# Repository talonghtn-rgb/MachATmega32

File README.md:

# ATmega32 Embedded Learning Board

<h2 align="center">
  THIẾT KẾ VÀ CHẾ TẠO BO MẠCH LẬP TRÌNH NHÚNG DỰA TRÊN VI ĐIỀU KHIỂN AVR CHO MỤC ĐÍCH GIÁO DỤC
</h2>

<p align="center">
  <b>ATmega32 Embedded Training Board</b>
</p>

---

##  Giới thiệu

Đây là dự án thiết kế và chế tạo **bo mạch học tập lập trình nhúng sử dụng vi điều khiển ATmega32**, được xây dựng nhằm phục vụ việc học tập, thực hành và nghiên cứu các hệ thống nhúng.

Bo mạch tích hợp nhiều ngoại vi phổ biến, giúp sinh viên có thể thực hành lập trình vi điều khiển, giao tiếp với cảm biến, thiết bị hiển thị, bộ nhớ và các chuẩn giao tiếp thông dụng.

Toàn bộ sơ đồ nguyên lý và PCB của bo mạch được thiết kế bằng **KiCad**.

---

##  Mục tiêu

- Thiết kế một bo mạch học tập dựa trên vi điều khiển **ATmega32**.
- Tích hợp các ngoại vi thường sử dụng trong các bài thực hành vi điều khiển.
- Hỗ trợ nhiều chuẩn giao tiếp như UART, I2C, SPI và 1-Wire.
- Thiết kế PCB hoàn chỉnh bằng KiCad.
- Xây dựng nền tảng phần cứng phục vụ các bài thực hành lập trình nhúng.
- Kiểm thử từng chức năng của bo mạch trên phần cứng thực tế.

---

##  Vi điều khiển:  ATmega32

##  Các ngoại vi tích hợp

Bo mạch được thiết kế với các khối chức năng:

| Ngoại vi | Chức năng |
|---|---|
| LCD 16x2 | Hiển thị thông tin |
| LED 7 đoạn 4 số | Hiển thị số |
| LM35 | Đo nhiệt độ |
| DS18B20 | Cảm biến nhiệt độ |
| DS3231 | Đồng hồ thời gian thực |
| Relay | Điều khiển thiết bị |
| Micro SD Card | Lưu trữ dữ liệu |
| LED đơn | Hiển thị trạng thái |
| Button | Nhập tín hiệu số |
| Potentiometer | Tạo tín hiệu analog |
| LDR | Đo cường độ ánh sáng |
| CH340E | Giao tiếp USB-UART |

Các ngoại vi trên được tích hợp nhằm phục vụ nhiều bài thực hành về GPIO, ADC, UART, I2C, SPI, 1-Wire và điều khiển thiết bị.

---

##  Các chuẩn giao tiếp
UART,I2C,SPI,1-Wire

##  Thiết kế bằng KiCad

Project được thiết kế bằng **KiCad 9**.

Các file chính:

```text
ATmega32/
│
├── atmega32.kicad_pro       # KiCad Project
├── atmega32.kicad_sch       # Schematic
├── atmega32.kicad_pcb       # PCB Layout
│
├── aa.kicad_sym             # Custom Symbol Library
│
├── CR1220 SMD.pretty/       # Footprint Library
├── Micro.pretty/            # Footprint Library
├── SN74LVC125APWR.pretty/   # Footprint Library
│
├── fp-lib-table
├── sym-lib-table
└── Logo_hus.png
```

## Hình ảnh sản phẩm trong quá trình làm
## Ghi chú: Hình ảnh ở trên là bản đầu tiên làm, file ở trên đã sửa sau khi test các chức năng sửa những lỗi cho ra bản hoàn chỉnh nhất.

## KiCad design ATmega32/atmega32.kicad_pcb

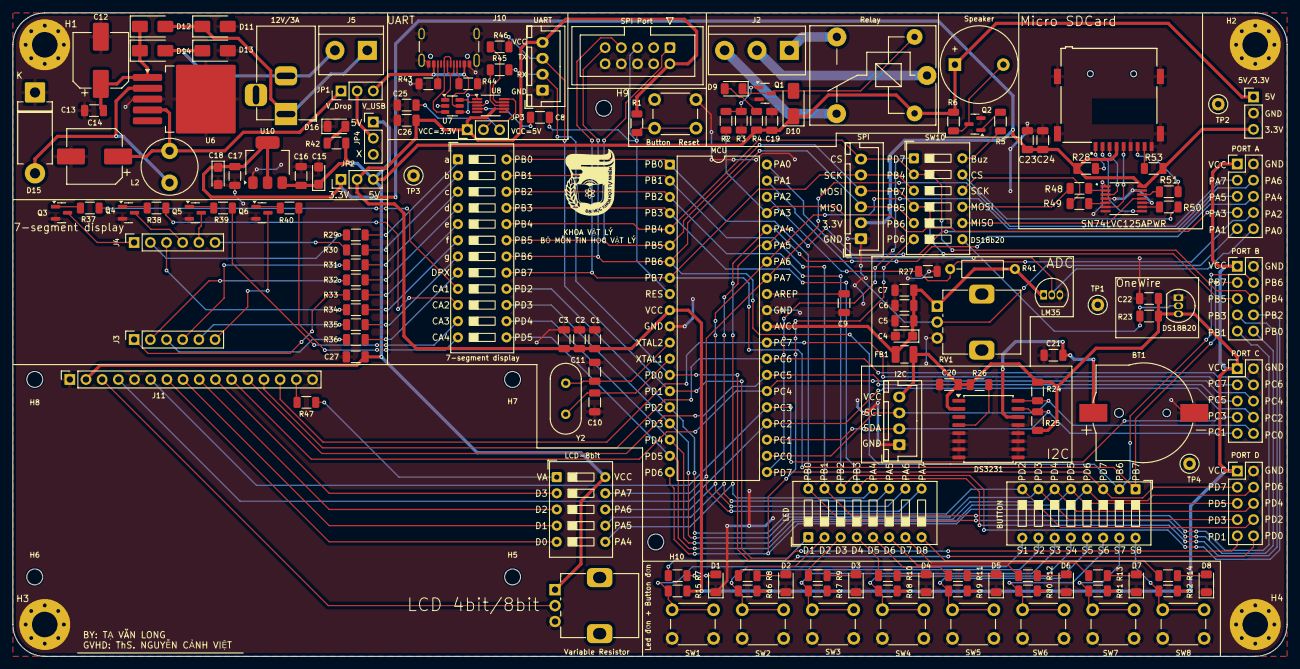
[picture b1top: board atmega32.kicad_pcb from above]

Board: 2 copper layers, 200.0 x 101.0 mm, 168 parts (0 on the bottom side), 145 nets.

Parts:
5V/3.3V: 5V/3.3V; PinHeader_1x03_P2.54mm_Vertical
7-segment display: LED7_DOAN_4SO; SW_DIP_SPSTx12_Slide_9.78x32.66mm_W7.62mm_P2.54mm
12V/3A: Barrel_Jack; BarrelJack_Horizontal
 : LOGO
BT1: PIN; BatteryHolder_RSPRO_2378296_1x1220
BUTTON: BUTTON_DON; SW_DIP_SPSTx08_Slide_9.78x22.5mm_W7.62mm_P2.54mm
Button  Reset: SW_Push; SW_PUSH_6mm_H5mm
C1, C2, C3, C5, C6, C7, C8, C9, C16, C17, C19, C20, C21, C22, C24, C26, C27: 100nF; C_1206_3216Metric
C4, C15, C18: 10uF; CP_EIA-3216-18_Kemet-A
C10, C11: 22pF; C_1206_3216Metric
C12: 440uF/35V; CP_Elec_8x10.5
C13: 1000nF; C_1206_3216Metric
C14: 330uF/35V; CP_Elec_8x10.5
C23: 10uF; C_1206_3216Metric
C25: 10nF; C_1206_3216Metric
D1, D2, D3, D4, D5, D6, D7, D8, D9, D16: LED; LED_1206_3216Metric
D10, D11, D12, D13, D14: 1N4007; D_SMA
D15: 1N5822; D_DO-201AD_P12.70mm_Horizontal
DS18B20: DS18B20; TO-92_Inline
DS3231: DS3231M; SOIC-16W_7.5x10.3mm_P1.27mm
FB1: FerriteBead; L_1210_3225Metric
H1: MH1; MountingHole_4mm_Pad_Via
H2: MH2; MountingHole_4mm_Pad_Via
H3: MH3; MountingHole_4mm_Pad_Via
H4: MH4; MountingHole_4mm_Pad_Via
H5: LCD1; MountingHole_2.5mm
H6: LCD2; MountingHole_2.5mm
H7: LCD3; MountingHole_2.5mm
H8: LCD4; MountingHole_2.5mm
H9: MH5; MountingHole_2.5mm
H10: MH6; MountingHole_2.5mm
I2C: SCL/SDA; JST_XH_B4B-XH-A_1x04_P2.50mm_Vertical
J1: Micro_SD_Card; GCT_MEM2075
J2: Screw_Terminal_01x03; TerminalBlock_bornier-3_P5.08mm
J3: 4-digit 7-segment_2; PinSocket_1x06_P2.54mm_Vertical
J4: 4-digit 7-segment_1; PinSocket_1x06_P2.54mm_Vertical
J5: Screw_Terminal_01x02; TerminalBlock_bornier-2_P5.08mm
J10: USB_C_Receptacle_USB2.0_16P; USB_C_Receptacle_GCT_USB4105-xx-A_16P_TopMnt_Horizontal
J11: Conn_01x16_lcd; PinSocket_1x16_P2.54mm_Vertical
JP1: Nguồn lọc or USB; PinHeader_1x03_P2.54mm_Vertical
JP2, JP3: 5V or 3.3V; PinHeader_1x03_P2.54mm_Vertical
JP4: 5V or x; PinHeader_1x03_P2.54mm_Vertical
L2: 33uH; L_Radial_D8.7mm_P5.00mm_Fastron_07HCP
LCD-8bit: SW_LCD_8bit; SW_DIP_SPSTx05_Slide_9.78x14.88mm_W7.62mm_P2.54mm
LED: LED_DON; SW_DIP_SPSTx08_Slide_9.78x22.5mm_W7.62mm_P2.54mm
LM35: LM35-LP; TO-92_Inline
MCU: ATmega32A-P; DIP-40_W15.24mm
PORT A: Port A; PinHeader_2x05_P2.54mm_Vertical
PORT B: Port B; PinHeader_2x05_P2.54mm_Vertical
PORT C: Port C; PinHeader_2x05_P2.54mm_Vertical
PORT D: Port D; PinHeader_2x05_P2.54mm_Vertical
Q1: MMBT2222A; SOT-23
Q2, Q3, Q4, Q5, Q6: BC846; SOT-23
R1, R15, R16, R17, R18, R19, R20, R21, R22, R26, R27, R37, R38, R39, R40: 10K; R_1206_3216Metric
R2, R5, R6, R45, R46: 1K; R_1206_3216Metric
R3: 10k; R_1206_3216Metric
R4: 470; R_1206_3216Metric
R7, R8, R9, R10, R11, R12, R13, R14: 330; R_1206_3216Metric
R23: 4.7k; R_1206_3216Metric
R24, R25, R28, R53: 4.7K; R_1206_3216Metric
R29, R30, R31, R32, R33, R34, R35, R36, R47: 220; R_1206_3216Metric
R41: GL5528 photoresistor; R_Axial_DIN0207_L6.3mm_D2.5mm_P10.16mm_Horizontal
R42: 2.2K; R_1206_3216Metric
R43, R44: 5k1; R_1206_3216Metric
R48, R49, R50, R51: 3.3K; R_1206_3216Metric
RV1: R_Potentiometer; Potentiometer_Alps_RK09K_Single_Vertical
Relay: SANYOU_SRD; Relay_SPDT_SANYOU_SRD_Series_Form_C
SN74LVC125APWR: SN74LVC125APWR; SOP65P640X120-14N
SPI: SPI; JST_XH_B6B-XH-A_1x06_P2.50mm_Vertical
SPI Port: AVR-ISP-10; IDC-Header_2x05_P2.54mm_Vertical
SW1, SW2, SW3, SW4, SW5, SW6, SW7, SW8: SW_Push; SW_PUSH_6mm_H5mm
SW10: SW_DIP_x06; SW_DIP_SPSTx06_Slide_9.78x17.42mm_W7.62mm_P2.54mm
Speaker: Buzzer; Buzzer_12x9.5RM7.6
TP1, TP2, TP3, TP4: TestPoint; TestPoint_Loop_D2.50mm_Drill1.0mm
U6: LM2596S-ADJ; TO-263-5_TabPin3
U7: USBLC6-2SC6; SOT-23-6
U8: CH340E; MSOP-10_3x3mm_P0.5mm
U10: LM1117MP-3.3; SOT-223-3_TabPin2
UART: TX/RX; JST_XH_B4B-XH-A_1x04_P2.50mm_Vertical
Variable Resistor: 10K; Potentiometer_Alps_RK09K_Single_Vertical
Y2: 8Mhz; Crystal_HC49-U_Vertical

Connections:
/Buz: R5.1, SW10.12
/CA1: J4.1, Q3.3 (C)
/CA2: J4.4, Q4.3 (C)
/CA3: J4.5, Q5.3 (C)
/CA4: J3.6, Q6.3 (C)
/CD: J1.2 (DAT3/CD), SN74LVC125APWR.8 (3Y)
/CLK: J1.5 (CLK), SN74LVC125APWR.6 (2Y)
/CMD: J1.3 (CMD), SN74LVC125APWR.3 (1Y)
/CS: R50.2, SW10.11
/D0: J1.7 (DAT0), R51.2
/D1: LED.1, R7.2
/D2: LED.2, R8.2
/D3: LED.3, R9.2
/D4: LED.4, R10.2
/D5: LED.5, R11.2
/D6: LED.6, R12.2
/D7: LED.7, R13.2
/D8: LED.8, R14.2
/DPX: J3.3, R36.2
/DS18b20: DS18B20.2 (DQ), R23.1, SW10.7
/LCD_D0: J11.7, LCD-8bit.5
/LCD_D1: J11.8, LCD-8bit.4
/LCD_D2: J11.9, LCD-8bit.3
/LCD_D3: J11.10, LCD-8bit.2
/LED7_D1: 7-segment display.9, R37.1
/LED7_D2: 7-segment display.10, R38.1
/LED7_D3: 7-segment display.11, R39.1
/LED7_D4: 7-segment display.12, R40.1
/LED7_DPX: 7-segment display.8, R36.1
/LED7_a: 7-segment display.1, R29.1
/LED7_b: 7-segment display.2, R30.1
/LED7_c: 7-segment display.3, R31.1
/LED7_d: 7-segment display.4, R32.1
/LED7_e: 7-segment display.5, R33.1
/LED7_f: 7-segment display.6, R34.1
/LED7_g: 7-segment display.7, R35.1
/MISO: SN74LVC125APWR.11 (4Y), SW10.8
/MOSI: R48.2, SW10.9
/PA0: LM35.2 (V_{OUT}), MCU.40 (PA0), PORT A.10
/PA1: MCU.39 (PA1), PORT A.9, RV1.2
/PA2: MCU.38 (PA2), PORT A.8, R27.1, R41.2
/PA3: MCU.37 (PA3), PORT A.7, R2.1
/PA4: LCD-8bit.6, LED.12, MCU.36 (PA4), PORT A.6
/PA5: LCD-8bit.7, LED.11, MCU.35 (PA5), PORT A.5
/PA6: LCD-8bit.8, LED.10, MCU.34 (PA6), PORT A.4
/PA7: LCD-8bit.9, LED.9, MCU.33 (PA7), PORT A.3
/PB0: 7-segment display.24, LED.16, MCU.1 (PB0), PORT B.10
/PB1: 7-segment display.23, LED.15, MCU.2 (PB1), PORT B.9
/PB2: 7-segment display.22, LED.14, MCU.3 (PB2), PORT B.8
/PB3: 7-segment display.21, LED.13, MCU.4 (PB3), PORT B.7
/PB4: 7-segment display.20, MCU.5 (PB4), PORT B.6, SPI.6, SW10.2
/PB5: 7-segment display.19, MCU.6 (PB5), PORT B.5, SPI.4, SPI Port.1 (MOSI), SW10.4
/PB6: 7-segment display.18, BUTTON.2, MCU.7 (PB6), PORT B.4, SPI.3, SPI Port.9 (MISO), SW10.5
/PB7: 7-segment display.17, BUTTON.1, MCU.8 (PB7), PORT B.3, SPI.5, SPI Port.7 (SCK), SW10.3
/PC0: DS3231.16 (SCL), I2C.3, MCU.22 (PC0), PORT C.10, R24.1
/PC1: DS3231.15 (SDA), I2C.2, MCU.23 (PC1), PORT C.9, R25.1
/PC2: J11.4, MCU.24 (PC2), PORT C.8
/PC3: J11.6, MCU.25 (PC3), PORT C.7
/PC4: J11.11, MCU.26 (PC4), PORT C.6
/PC5: J11.12, MCU.27 (PC5), PORT C.5
/PC6: J11.13, MCU.28 (PC6), PORT C.4
/PC7: J11.14, MCU.29 (PC7), PORT C.3
/PD0: MCU.14 (PD0), PORT D.10, R45.2, UART.2
/PD1: MCU.15 (PD1), PORT D.9, R46.2, UART.3
/PD2: 7-segment display.16, BUTTON.8, MCU.16 (PD2), PORT D.8
/PD3: 7-segment display.15, BUTTON.7, MCU.17 (PD3), PORT D.7
/PD4: 7-segment display.14, BUTTON.6, MCU.18 (PD4), PORT D.6
/PD5: 7-segment display.13, BUTTON.5, MCU.19 (PD5), PORT D.5
/PD6: BUTTON.4, MCU.20 (PD6), PORT D.4, SW10.6
/PD7: BUTTON.3, MCU.21 (PD7), PORT D.3, SW10.1
/S1: BUTTON.9, R15.1, SW1.1
/S2: BUTTON.10, R16.1, SW2.1
/S3: BUTTON.11, R17.1, SW3.1
/S4: BUTTON.12, R18.1, SW4.1
/S5: BUTTON.13, R19.1, SW5.1
/S6: BUTTON.14, R20.1, SW6.1
/S7: BUTTON.15, R21.1, SW7.1
/S8: BUTTON.16, R22.1, SW8.1
/SCK: R49.2, SW10.10
/VA: LCD-8bit.1, R47.1
/a: J4.2, R29.2
/b: J4.6, R30.2
/c: J3.4, R31.2
/d: J3.2, R32.2
/e: J3.1, R33.2
/f: J4.3, R34.2
/g: J3.5, R35.2
/reset: Button Reset.2, C8.2, MCU.9 (~RESET), R1.2, SPI Port.5 (~RST)
AVCC: C4.1, C5.1, C6.1, C7.1, FB1.2, LM35.1 (+V_{S}), MCU.30 (AVCC), R41.1, RV1.1
GND: 5V/3.3V.2, BT1.2 (-), Button Reset.1, C1.1, C2.1, C3.1, C4.2, C5.2, C6.2, C7.2, C9.1, C10.1, C11.1, C12.2, C13.1, C14.2, C15.2, C16.1, C17.2, C18.2, C19.1, C20.1, C21.1, C22.2, C23.2, C24.2, C25.2, C26.2, C27.2, D1.1 (K), D2.1 (K), D3.1 (K), D4.1 (K), D5.1 (K), D6.1 (K), D7.1 (K), D8.1 (K), D11.2 (A), D13.2 (A), D15.1 (K), D16.1 (K), DS18B20.1 (GND), DS3231.5 (GND), DS3231.6 (GND), DS3231.7 (GND), DS3231.8 (GND), DS3231.9 (GND), DS3231.10 (GND), DS3231.11 (GND), DS3231.12 (GND), DS3231.13 (GND), H1.1, H2.1, H3.1, H4.1, I2C.1, J1.6 (VSS), J1.9 (SHIELD), J10.A1 (GND), J10.A12 (GND), J10.B1 (GND), J10.B12 (GND), J10.S1 (SHIELD), J11.1, J11.5, J11.16, LM35.3 (GND), MCU.11 (GND), MCU.31 (GND), PORT A.2, PORT B.2, PORT C.2, PORT D.2, Q1.2 (E), Q2.2 (E), Q3.2 (E), Q4.2 (E), Q5.2 (E), Q6.2 (E), R3.2, R27.2, R43.2, R44.2, RV1.3, SN74LVC125APWR.1 (1~OE), SN74LVC125APWR.4 (2~OE), SN74LVC125APWR.7 (GND), SN74LVC125APWR.10 (3~OE), SN74LVC125APWR.13 (4~OE), SPI.1, SPI Port.4 (GND), SPI Port.6 (GND), SPI Port.8 (GND), SPI Port.10 (GND), SW1.2, SW2.2, SW3.2, SW4.2, SW5.2, SW6.2, SW7.2, SW8.2, TP1.1, TP2.1, TP3.1, TP4.1, U6.3 (GND), U7.2 (GND), U8.3 (GND), U10.1 (GND), UART.1, Variable Resistor.3
unnamed: BT1.1 (+), C21.2, DS3231.14 (VBAT)
unnamed: D1.2 (A), R7.1
unnamed: D2.2 (A), R8.1
unnamed: D3.2 (A), R9.1
unnamed: D4.2 (A), R10.1
unnamed: D5.2 (A), R11.1
unnamed: D6.2 (A), R12.1
unnamed: D7.2 (A), R13.1
unnamed: D8.2 (A), R14.1
unnamed: D9.2 (A), R4.2
unnamed: D9.1 (K), D10.2 (A), Q1.3 (C), Relay.2
unnamed: 12V/3A.1, D11.1 (K), D12.2 (A), J5.1
unnamed: C12.1, C13.2, D12.1 (K), D14.1 (K), U6.1 (VIN)
unnamed: 12V/3A.2, D13.1 (K), D14.2 (A), J5.2
unnamed: D15.2 (A), L2.1, U6.2 (OUT)
unnamed: D16.2 (A), R42.1
unnamed: J1.8 (DAT1), R53.2
unnamed: J1.1 (DAT2), R28.2
unnamed: J2.1, Relay.3
unnamed: J2.2, Relay.1
unnamed: J2.3, Relay.4
unnamed: J10.A5 (CC1), R44.1
unnamed: J10.B5 (CC2), R43.1
unnamed: J10.A6 (D+), J10.B6 (D+), U7.3 (I/O2)
unnamed: J10.A7 (D-), J10.B7 (D-), U7.1 (I/O1)
unnamed: J11.3, Variable Resistor.2
unnamed: J11.15, R47.2
unnamed: C14.1, JP1.1 (A), L2.2, U6.4 (FB)
unnamed: JP1.2 (C), JP4.2 (C)
unnamed: C25.1, JP3.3 (B)
unnamed: JP3.2 (C), U8.10 (V3)
unnamed: Q1.1 (B), R2.2, R3.1
unnamed: Q2.1 (B), R5.2
unnamed: Q2.3 (C), R6.1, Speaker.2 (-)
unnamed: Q3.1 (B), R37.2
unnamed: Q4.1 (B), R38.2
unnamed: Q5.1 (B), R39.2
unnamed: Q6.1 (B), R40.2
unnamed: C9.2, MCU.32 (AREF)
unnamed: C10.2, MCU.13 (XTAL1), Y2.2
unnamed: C11.2, MCU.12 (XTAL2), Y2.1
unnamed: DS3231.4 (~RST), R26.2
unnamed: R46.1, U8.9 (RXD)
unnamed: R45.1, U8.8 (TXD)
unnamed: U7.4 (I/O2), U8.1 (UD+)
unnamed: U7.6 (I/O1), U8.2 (UD-)
unnamed: C8.1, U8.4 (~RTS)
unnamed: R48.1, SN74LVC125APWR.2 (1A)
unnamed: R49.1, SN74LVC125APWR.5 (2A)
unnamed: R50.1, SN74LVC125APWR.9 (3A)
unnamed: R51.1, SN74LVC125APWR.12 (4A)
VCC-3.3V: 5V/3.3V.3, C17.1, C18.1, C23.1, C24.1, J1.4 (VDD), JP2.1 (A), R28.1, R53.1, SN74LVC125APWR.14 (VCC), SPI.2, U10.2 (VO)
VCC-5V: 5V/3.3V.1, C15.1, C16.2, C19.2, C27.1, D10.1 (K), J11.2, JP2.3 (B), JP4.1 (A), LCD-8bit.10, R4.1, R6.2, R42.2, Relay.5, Speaker.1 (+), U10.3 (VI), Variable Resistor.1
VCC-BRD: C1.2, C2.2, C3.2, C20.2, C22.1, C26.1, DS18B20.3 (V_{DD}), DS3231.2 (VCC), FB1.1, I2C.4, JP2.2 (C), JP3.1 (A), MCU.10 (VCC), PORT A.1, PORT B.1, PORT C.1, PORT D.1, R1.1, R15.2, R16.2, R17.2, R18.2, R19.2, R20.2, R21.2, R22.2, R23.2, R24.2, R25.2, R26.1, SPI Port.2 (VCC), U8.7 (VCC), UART.4
VCC_USB: J10.A4 (VBUS), J10.A9 (VBUS), J10.B4 (VBUS), J10.B9 (VBUS), JP1.3 (B), U7.5 (VBUS)
